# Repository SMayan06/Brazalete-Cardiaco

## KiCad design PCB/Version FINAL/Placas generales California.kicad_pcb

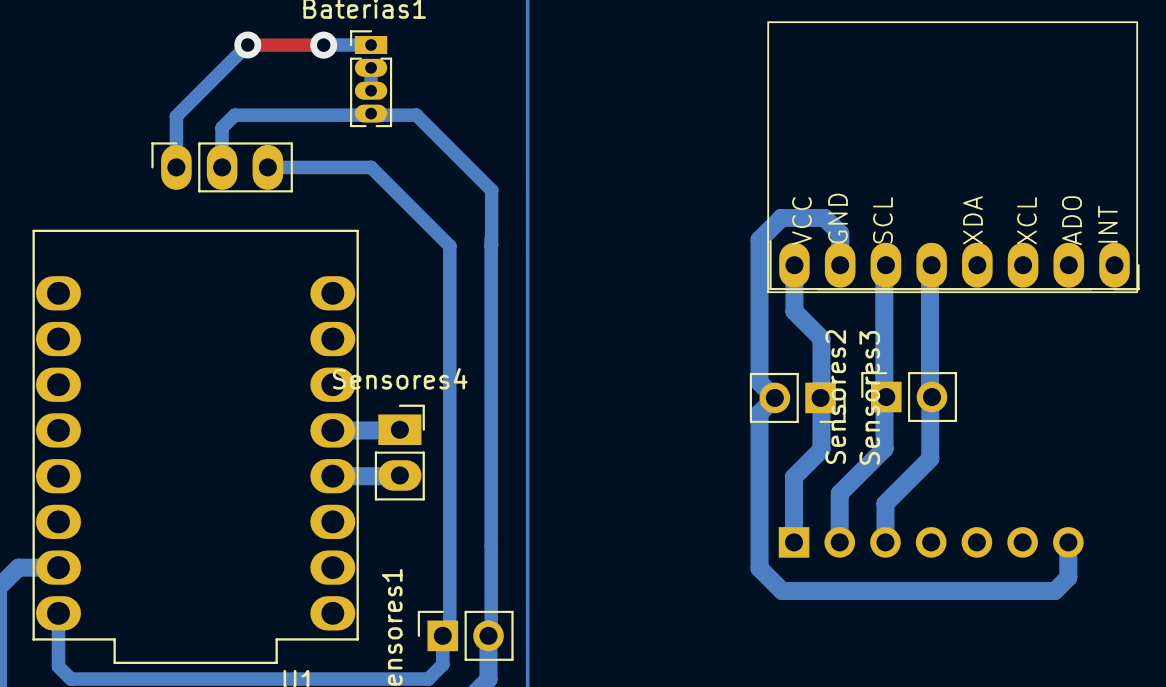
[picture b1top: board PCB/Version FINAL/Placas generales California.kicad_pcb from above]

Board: 2 copper layers, 9 parts (1 on the bottom side), 6 nets.

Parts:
Baterias1: Conn_01x04_Pin; PinHeader_1x04_P1.27mm_Vertical
J3: L7805; PinSocket_1x03_P2.54mm_Vertical
MPU1: MPU6050
Sensores1, Sensores2, Sensores3, Sensores4: Conn_01x02_Socket; PinSocket_1x02_P2.54mm_Vertical
U1: ESP32-C3_SUPERMINI_TH; MODULE_ESP32-C3_SUPERMINI
U2: max30102

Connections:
+5V: J3.3, MPU1.1, Sensores1.1, Sensores3.1, U1.5V, U2.1 (VIN)
GND: Baterias1.4, J3.2, MPU1.2, Sensores1.2, Sensores3.2, U1.G (GND), U2.7 (GND)
unnamed: Baterias1.1, J3.1
unnamed: Baterias1.2, Baterias1.3
SCL: MPU1.3, Sensores2.1, Sensores4.1, U1.9 (GPIO9), U2.2 (SCL)
SDA: MPU1.4, Sensores2.2, Sensores4.e (Pin_2), U1.8 (GPIO8), U2.3 (SDA)

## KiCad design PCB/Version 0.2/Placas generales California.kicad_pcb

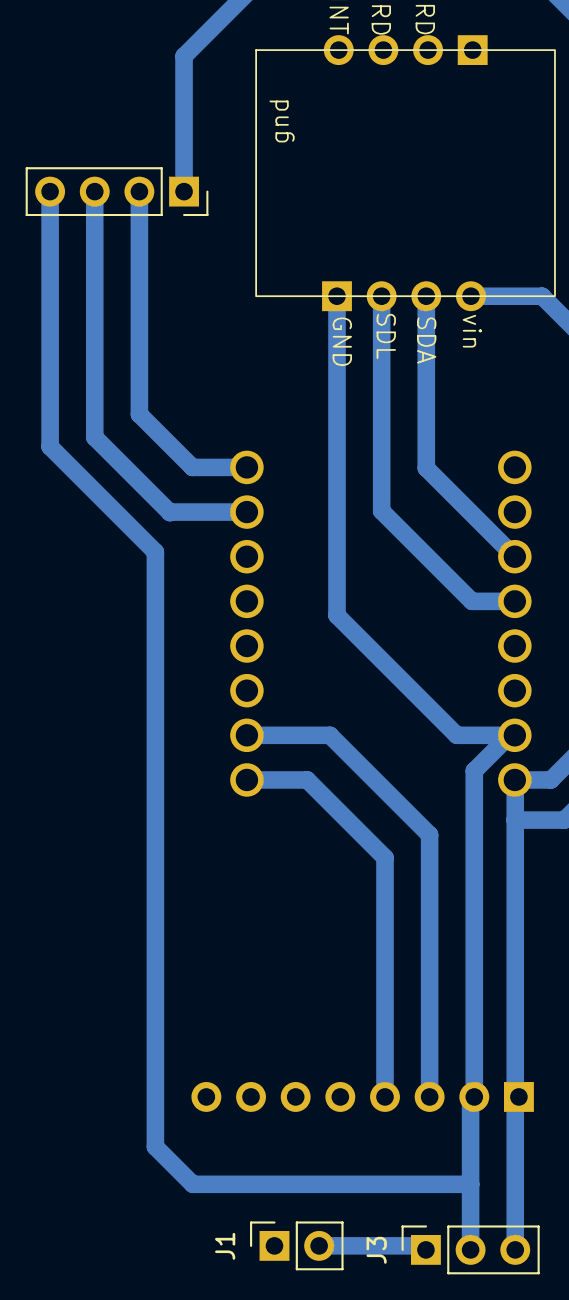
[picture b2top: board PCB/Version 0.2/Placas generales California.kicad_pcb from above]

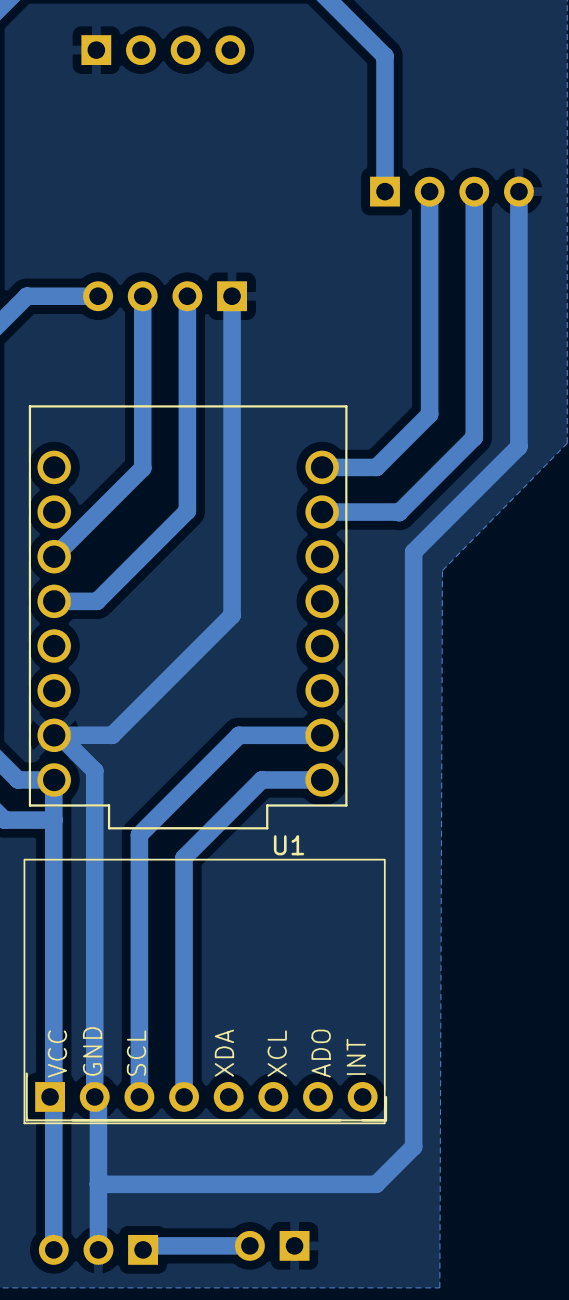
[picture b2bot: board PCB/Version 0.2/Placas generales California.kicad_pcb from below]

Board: 2 copper layers, 6 parts (2 on the bottom side), 9 nets.

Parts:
J1: 7.4; PinSocket_1x02_P2.54mm_Vertical
J2: GPS; PinSocket_1x04_P2.54mm_Vertical
J3: L7805; PinSocket_1x03_P2.54mm_Vertical
MPU1: MPU6050
U1: ESP32-C3_SUPERMINI_TH; MODULE_ESP32-C3_SUPERMINI
U2: Max30102

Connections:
+5V: J2.1, J3.3, MPU1.1, U1.5V, U2.4
GND: J1.1, J2.4, J3.2, MPU1.2, U1.G (GND), U2.1, U2.5
unnamed: J1.2, J3.1
RX: J2.2, U1.21 (GPIO21)
SCL: MPU1.3, U1.6 (GPIO6)
SCLM: U1.3 (GPIO3), U2.2
SDA: MPU1.4, U1.5 (GPIO5)
SDAM: U1.2 (GPIO2), U2.3
TX: J2.3, U1.20 (GPIO20)

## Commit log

2025-10-02 Incorporacion del codigo (incompleto)
2025-11-17 pre-push
    actualizacion previa antes de subirlo a github.
